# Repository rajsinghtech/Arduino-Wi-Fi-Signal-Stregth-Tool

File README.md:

# Arduino-Wi-Fi-Signal-Strength-Tool

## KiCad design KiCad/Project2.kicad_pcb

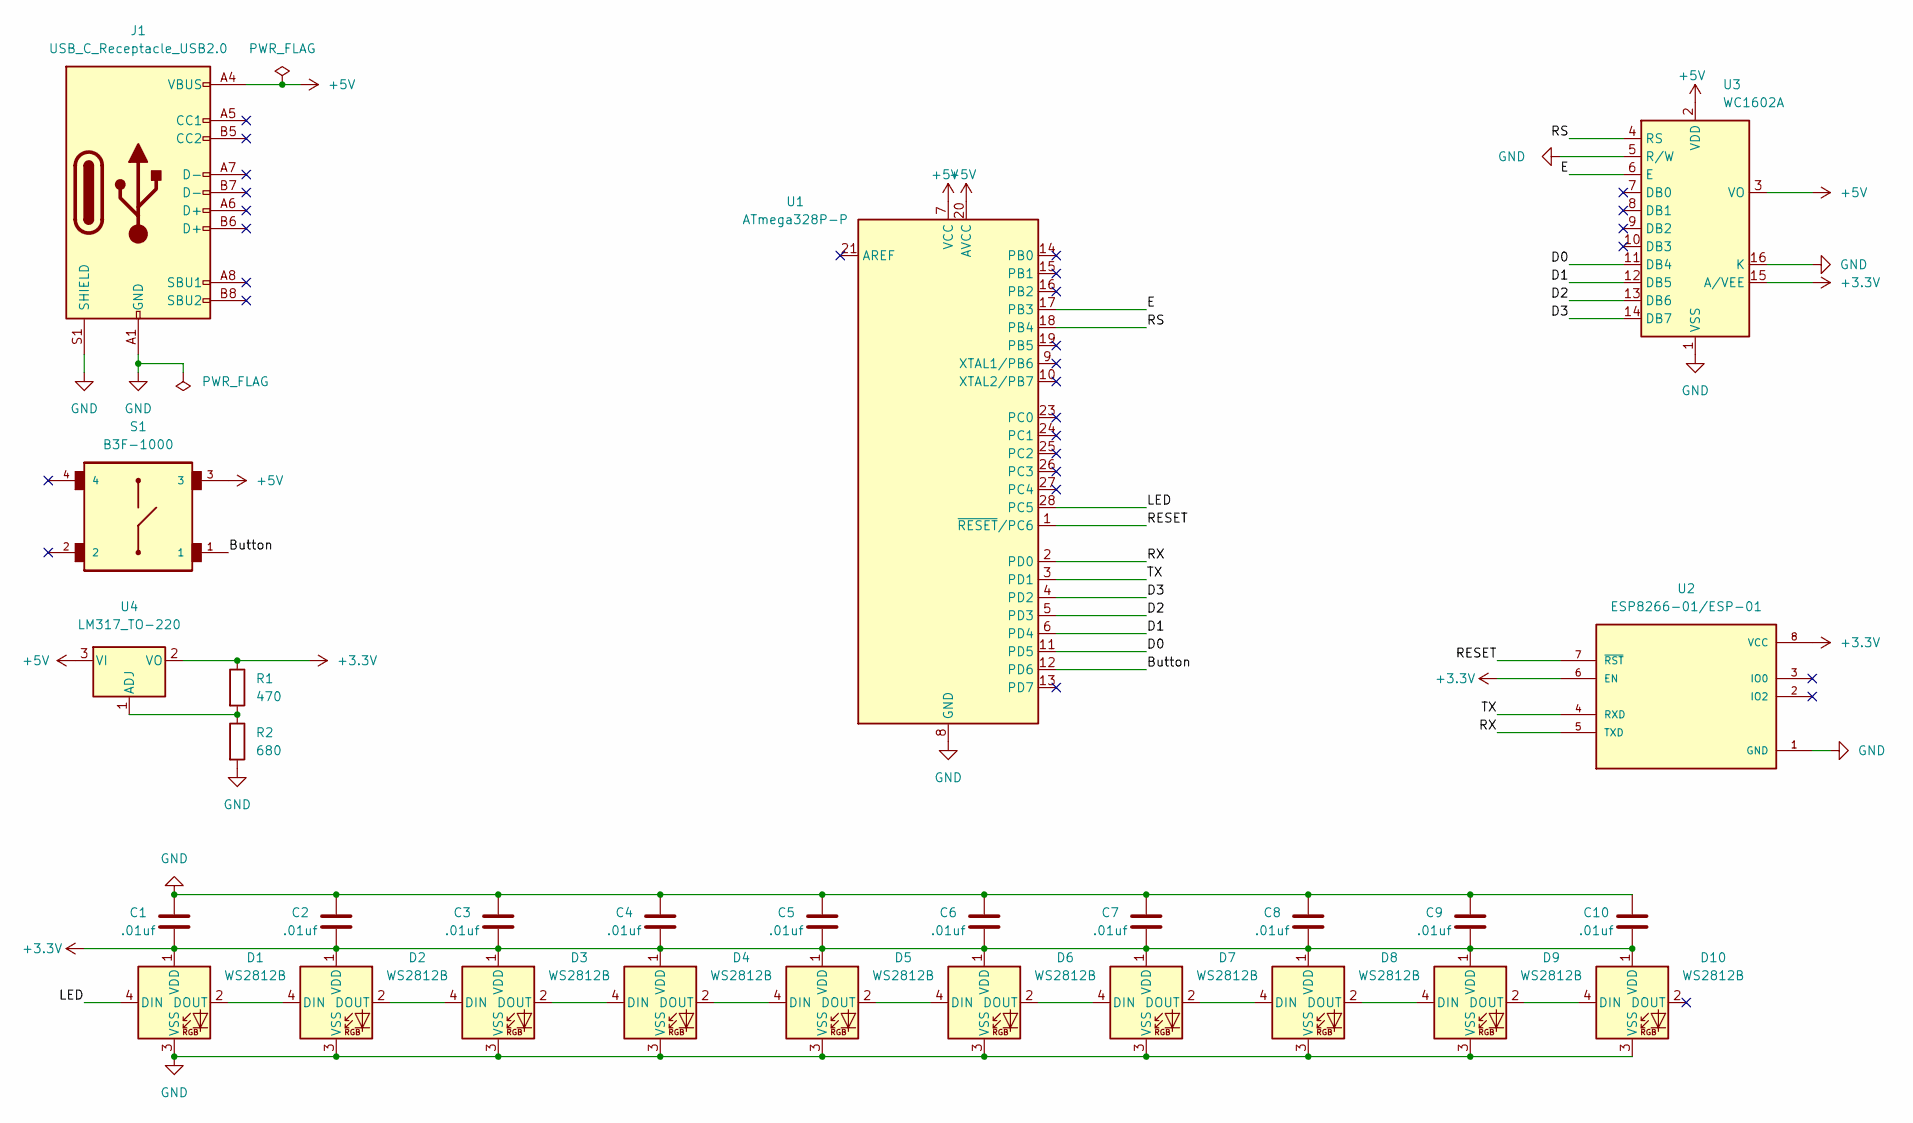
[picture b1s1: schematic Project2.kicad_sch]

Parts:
C1, C2, C3, C4, C5, C6, C7, C8, C9, C10: .01uf; CAPC2012X140N
D1, D2, D3, D4, D5, D6, D7, D8, D9, D10: WS2812B; LED_WS2812B_PLCC4_5.0x5.0mm_P3.2mm
J1: USB_C_Receptacle_USB2.0; USB_C_Receptacle_GCT_USB4085
R1: 470; R_Axial_DIN0207_L6.3mm_D2.5mm_P10.16mm_Horizontal
R2: 680; R_Axial_DIN0207_L6.3mm_D2.5mm_P10.16mm_Horizontal
S1: B3F-1000; SW_B3F-1000
U1: ATmega328P-P; DIP-28_W7.62mm
U2: ESP8266-01/ESP-01; XCVR_ESP8266-01/ESP-01; PARTREV V1.2
U3: WC1602A
U4: LM317_TO-220; TO-220-3_Vertical

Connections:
+3.3V: C1.2, C2.2, C3.2, C4.2, C5.2, C6.2, C7.2, C8.2, C9.2, C10.2, D1.1 (VDD), D2.1 (VDD), D3.1 (VDD), D4.1 (VDD), D5.1 (VDD), D6.1 (VDD), D7.1 (VDD), D8.1 (VDD), D9.1 (VDD), D10.1 (VDD), R1.1, U2.6 (EN), U2.8 (VCC), U3.15 (A/VEE), U4.2 (VO)
+5V: J1.A4 (VBUS), J1.A9 (VBUS), J1.B4 (VBUS), J1.B9 (VBUS), S1.3, U1.7 (VCC), U1.20 (AVCC), U3.2 (VDD), U3.3 (VO), U4.3 (VI)
/Button: S1.1, U1.12 (PD6)
/D0: U1.11 (PD5), U3.11 (DB4)
/D1: U1.6 (PD4), U3.12 (DB5)
/D2: U1.5 (PD3), U3.13 (DB6)
/D3: U1.4 (PD2), U3.14 (DB7)
/E: U1.17 (PB3), U3.6 (E)
/LED: D1.4 (DIN), U1.28 (PC5)
/RESET: U1.1 (~RESET/PC6), U2.7 (~RST)
/RS: U1.18 (PB4), U3.4 (RS)
/RX: U1.2 (PD0), U2.5 (TXD)
/TX: U1.3 (PD1), U2.4 (RXD)
GND: C1.1, C2.1, C3.1, C4.1, C5.1, C6.1, C7.1, C8.1, C9.1, C10.1, D1.3 (VSS), D2.3 (VSS), D3.3 (VSS), D4.3 (VSS), D5.3 (VSS), D6.3 (VSS), D7.3 (VSS), D8.3 (VSS), D9.3 (VSS), D10.3 (VSS), J1.A1 (GND), J1.A12 (GND), J1.B1 (GND), J1.B12 (GND), J1.S1 (SHIELD), R2.2, U1.8 (GND), U1.22 (GND), U2.1 (GND), U3.1 (VSS), U3.5 (R/W), U3.16 (K)
unnamed: D1.2 (DOUT), D2.4 (DIN)
unnamed: D2.2 (DOUT), D3.4 (DIN)
unnamed: D3.2 (DOUT), D4.4 (DIN)
unnamed: D4.2 (DOUT), D5.4 (DIN)
unnamed: D5.2 (DOUT), D6.4 (DIN)
unnamed: D6.2 (DOUT), D7.4 (DIN)
unnamed: D7.2 (DOUT), D8.4 (DIN)
unnamed: D8.2 (DOUT), D9.4 (DIN)
unnamed: D9.2 (DOUT), D10.4 (DIN)
unnamed: R1.2, R2.1, U4.1 (ADJ)

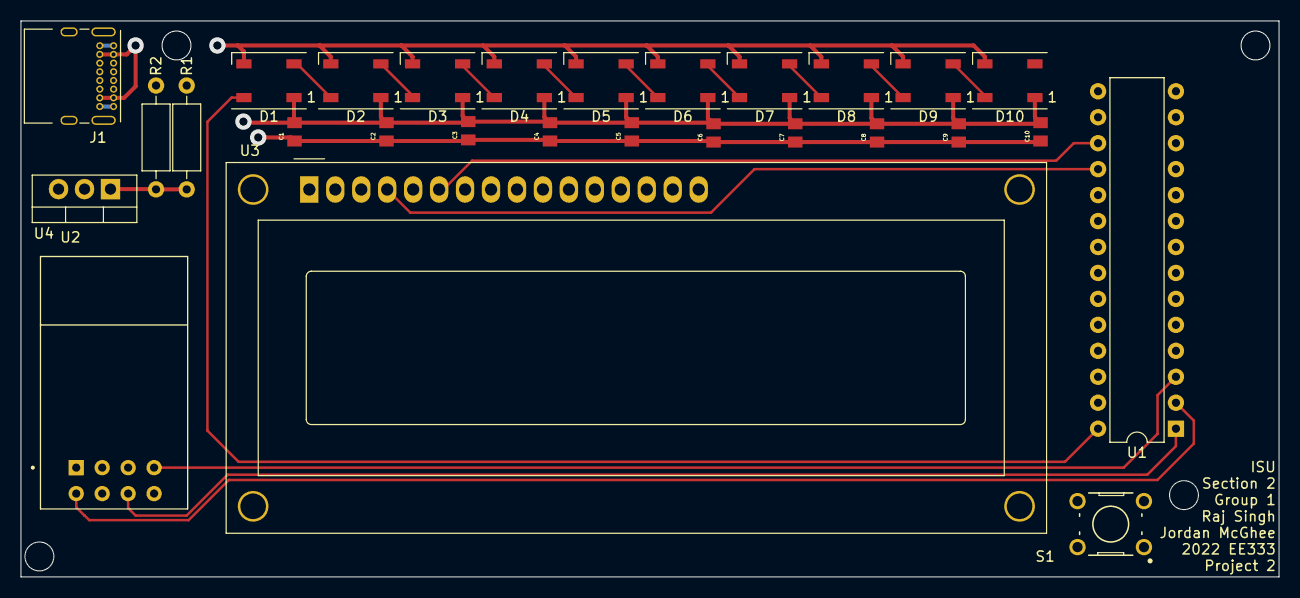
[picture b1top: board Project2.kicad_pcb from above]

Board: 4 copper layers, 123.1 x 54.4 mm, 28 parts (0 on the bottom side), 24 nets.

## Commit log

2022-12-12 Init
2022-12-12 Rename
